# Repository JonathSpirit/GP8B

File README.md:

# GP8B - GProcessor8Bits

Copyright (C) 2022 Guillaume Guillet\
Licensed under CERN-OHL-W v2 or later

<table border="0px">
<tr>
<td>
This source describes Open Hardware and is licensed under the CERN-OHL-W v2 or later.
</td>
</tr>
<tr>
<td>
You may redistribute and modify this documentation and make products
using it under the terms of the CERN-OHL-W v2 (https:/cern.ch/cern-ohl).
This documentation is distributed WITHOUT ANY EXPRESS OR IMPLIED
WARRANTY, INCLUDING OF MERCHANTABILITY, SATISFACTORY QUALITY
AND FITNESS FOR A PARTICULAR PURPOSE. Please see the CERN-OHL-W v2
for applicable conditions.
</td>
</tr>
</table>

Made with [Kicad](https://kicad.org/)

## Description
G_Processor8Bits is a homemade, without any microcontroller, 8bits processor.

## Stats

\
\
\

## Block diagram

[Block diagram (.pdf)](documents/blockDiagram/GP8B_blockDiagram.pdf)

## Instruction sets
GP8B follow [CodeG_binary (revision 1)](https://github.com/JonathSpirit/GComputer_standard)

8bits instuction is separated in 2 category :
```
-------------- Argument selection
|||  
||| ---------- Opcode
||| |||||
000 00000
```
**5bits for opcode :**
```
OPCODE      HEX     NAME            DESCRIPTION
xxx0’0000   0x00    BWRITE1_CLK     Apply value to bus “write 1”.
xxx0’0001   0x01    BWRITE2_CLK     Apply value to bus “write 2”.
xxx0’0010   0x02    BPCS_CLK        Apply value to bus “peripheral CS”.
xxx0’0011   0x03    OPLEFT_CLK      Apply value to the left operation.
xxx0’0100   0x04    OPRIGHT_CLK     Apply value to the right operation.
xxx0’0101   0x05    OPCHOOSE_CLK    Apply value for choosing the operation.
xxx0’0110   0x06    PERIPHERAL_CLK  Send a clock pulse to the peripheral.
xxx0’0111   0x07    BJMPSRC1_CLK    Apply value to bus “jump source 1”.
xxx0’1000   0x08    BJMPSRC2_CLK    Apply value to bus “jump source 2”.
xxx0’1001   0x09    BJMPSRC3_CLK    Apply value to bus “jump source 3”.
xxx0’1010   0x0A    JMPSRC_CLK      Jump to the address of “jump source”.
xxx0’1011   0x0B    BRAMADD1_CLK    Apply value to bus “RAM address 1”.
xxx0’1100   0x0C    BRAMADD2_CLK    Apply value to bus “RAM address 2”.
xxx0’1101   0x0D    SPI_CLK         Send a clock pulse for the SPI.
xxx0’1110   0x0E    BCFG_SPI_CLK    Apply value to the config bus SPI.
xxx0’1111   0x0F    STICK           Simple tick, do nothing (delay).
xxx1’0000   0x10    IF              Conditional instruction.
xxx1’0001   0x11    IFNOT           Conditional instruction inverted.
xxx1’0010   0x12    RAMW            Write value to the actual address of the memory.
xxx1’0011   0x13    UOP             Undefined operation.
xxx1’0100   0x14    UOP             Undefined operation.
xxx1’0101   0x15    UOP             Undefined operation.
xxx1’0110   0x16    UOP             Undefined operation.
xxx1’0111   0x17    LTICK           Long tick, do nothing (delay).
```
**3bits for argument selection :**
```
OPCODE      HEX     NAME            DESCRIPTION
000x’xxxx   0x00    SRCVALUE        The value stored to the source.
001x’xxxx   0x20    BREAD1          The value of the read bus 1.
010x’xxxx   0x40    BREAD2          The value of the read bus 2.
011x’xxxx   0x60    OPRESULT        The value of the operation result (ALU).
100x’xxxx   0x80    RAMVALUE        The value of the processor memory.
101x’xxxx   0xA0    SPI             The value of the SPI.
110x’xxxx   0xC0    EXT_1           External value 1.
111x’xxxx   0xE0    EXT_2           External value 2.
```

## Processor standard
This processor, follow the [SPS1](https://github.com/JonathSpirit/GComputer_standard) standard

## Compatibility
Compatible with all motherboard following the [MOM1_SPS1](https://github.com/JonathSpirit/GComputer_standard) standard

## Documents
[Block diagram (.pdf)](documents/blockDiagram/GP8B_blockDiagram.pdf)

[Schematics (.pdf)](documents/GP8B_schematics.pdf)

[Materials (.pdf)](documents/GP8B_materials.pdf)

[Datasheet (.pdf)](documents/GP8B_datasheet.pdf)

## Contributing / Questions
Please see [Contributing file](CONTRIBUTING.md)

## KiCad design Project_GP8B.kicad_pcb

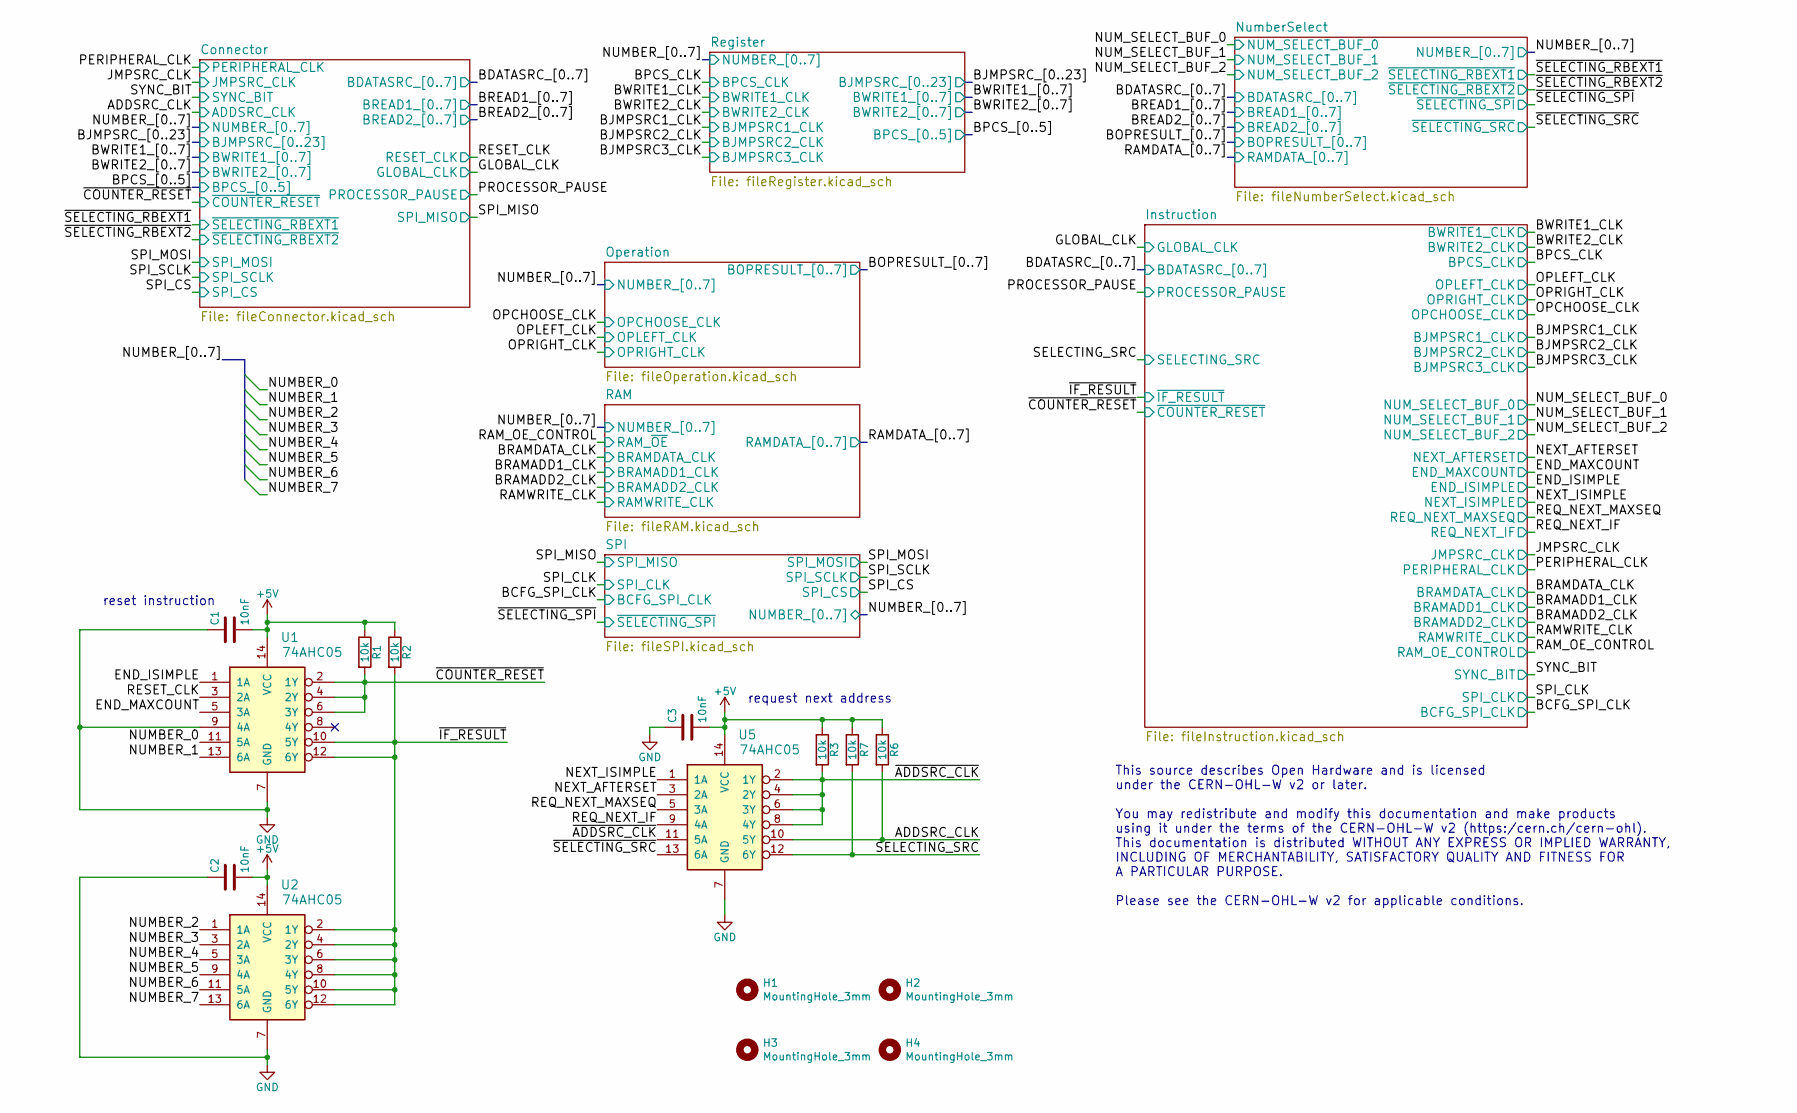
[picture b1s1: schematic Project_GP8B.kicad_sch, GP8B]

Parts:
C1, C2, C3: 10nF; C_0805_2012Metric
H1, H2, H3, H4: MountingHole_3mm
R1, R2, R3, R6, R7: 10k; R_0805_2012Metric
U1, U2, U5: 74AHC05; SOIC-14_3.9x8.7mm_P1.27mm

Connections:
+5V: C1.2, C2.2, C3.2, R1.1, R2.1, R3.1, R6.1, R7.1, U1.14 (VCC), U2.14 (VCC), U5.14 (VCC); also elsewhere on the board
/END_ISIMPLE: U1.1 (1A); also elsewhere on the board
/NEXT_AFTERSET: U5.3 (2A); also elsewhere on the board
/NEXT_IF: U5.9 (4A); also elsewhere on the board
/NEXT_ISIMPLE: U5.1 (1A); also elsewhere on the board
/NUMBER_0: U1.11 (5A); also elsewhere on the board
/NUMBER_1: U1.13 (6A); also elsewhere on the board
/NUMBER_2: U2.1 (1A); also elsewhere on the board
/NUMBER_3: U2.3 (2A); also elsewhere on the board
/NUMBER_4: U2.5 (3A); also elsewhere on the board
/NUMBER_5: U2.9 (4A); also elsewhere on the board
/NUMBER_6: U2.11 (5A); also elsewhere on the board
/NUMBER_7: U2.13 (6A); also elsewhere on the board
/RESET_CLK: U1.3 (2A); also elsewhere on the board
/~COUNTER_RESET: R1.2, U1.2 (1Y), U1.4 (2Y), U1.6 (3Y); also elsewhere on the board
/~SELECTING_SRC: U5.13 (6A); also elsewhere on the board

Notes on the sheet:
reset instruction
request next address
This source describes Open Hardware and is licensed under the CERN-OHL-W v2 or later. You may redistribute and modify this documentation and make products using it under the terms of the CERN-OHL-W v2 (https:/cern.ch/cern-ohl). This documentation is distributed WITHOUT ANY EXPRESS OR IMPLIED WARRAN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

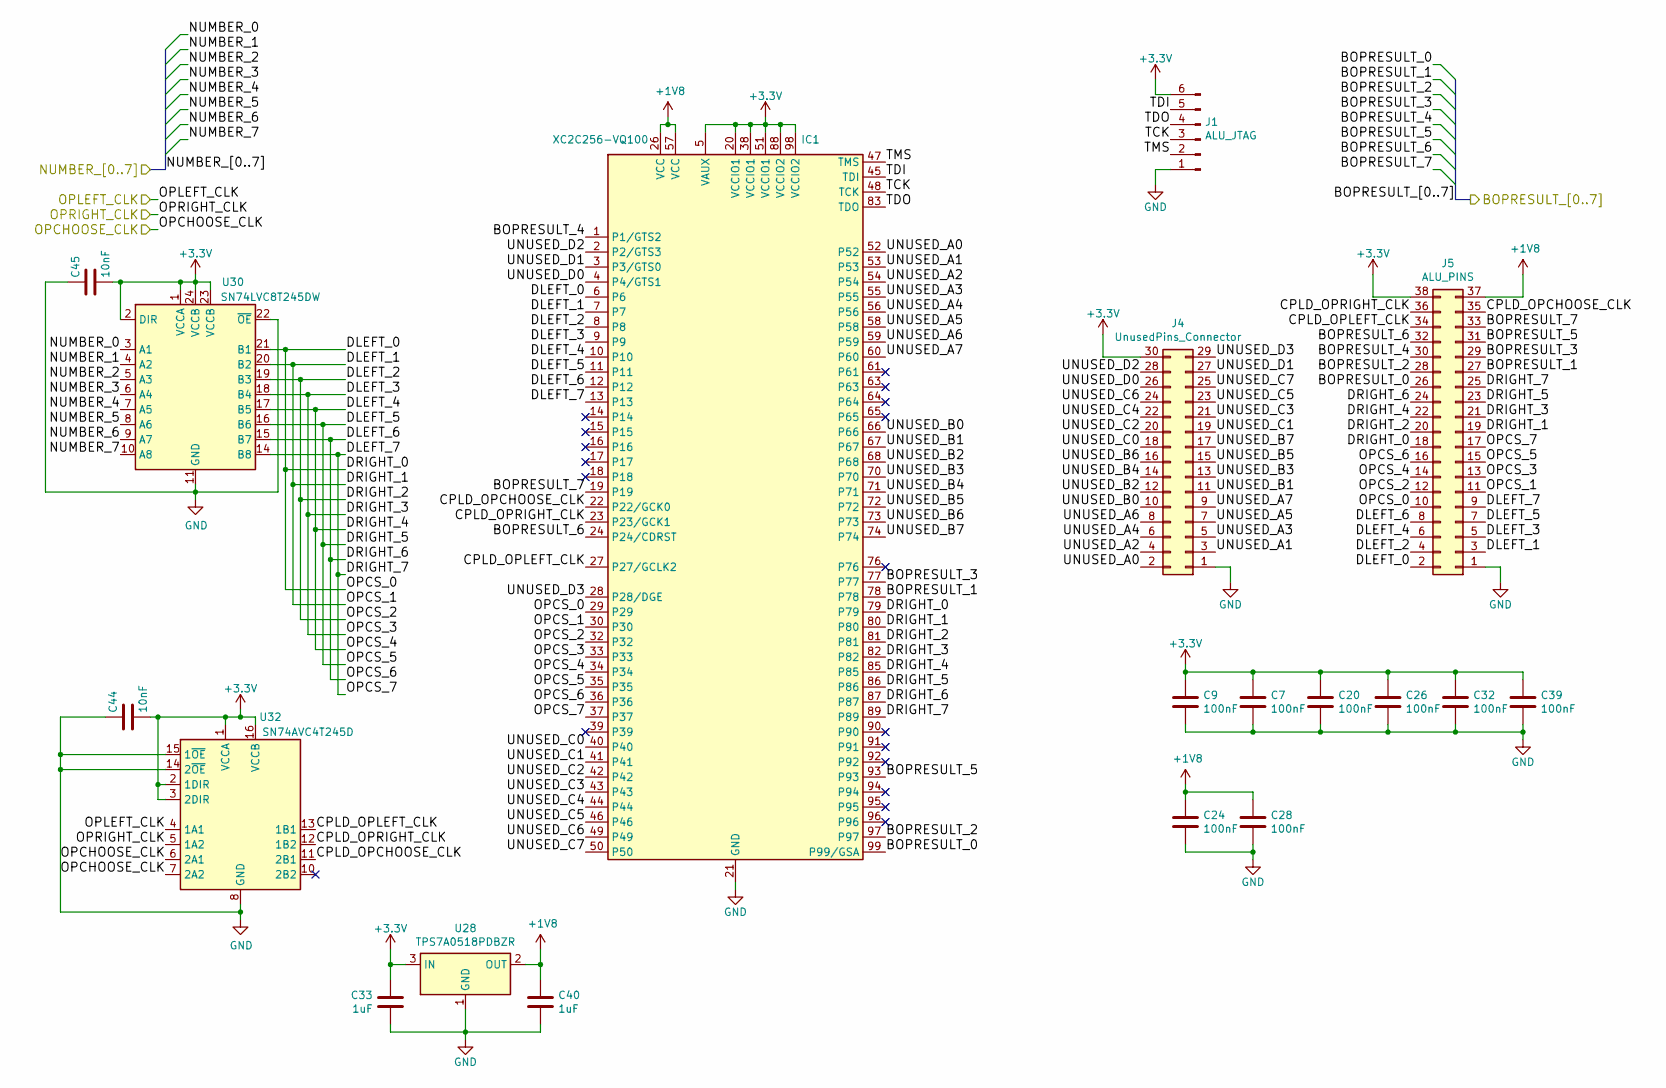
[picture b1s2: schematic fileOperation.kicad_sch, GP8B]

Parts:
C7, C9, C20, C24, C26, C28, C32, C39: 100nF; C_0805_2012Metric
C33, C40: 1uF; C_0805_2012Metric
C44, C45: 10nF; C_0805_2012Metric
IC1: XC2C256-VQ100; VQFP-100_14x14mm_P0.5mm
J1: ALU_JTAG; PinHeader_1x06_P2.54mm_Vertical
J4: UnusedPins_Connector; PinHeader_2x15_P1.27mm_Vertical
J5: ALU_PINS; PinHeader_2x19_P1.27mm_Vertical
U28: TPS7A0518PDBZR; SOT-23
U30: SN74LVC8T245DW; SOIC-24W_7.5x15.4mm_P1.27mm
U32: SN74AVC4T245D; SOIC-16_3.9x9.9mm_P1.27mm

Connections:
+1V8: C24.1, C28.1, C40.1, IC1.26 (VCC), IC1.57 (VCC), J5.37, U28.2 (OUT)
+3V3: C7.1, C9.1, C20.1, C26.1, C32.1, C33.1, C39.1, C44.2, C45.2, IC1.5 (VAUX), IC1.20 (VCCIO1), IC1.38 (VCCIO1), IC1.51 (VCCIO1), IC1.88 (VCCIO2), IC1.98 (VCCIO2), J1.6, J4.30, J5.38, U28.3 (IN), U30.1 (VCCA), U30.2 (DIR), U30.23 (VCCB), U30.24 (VCCB), U32.1 (VCCA), U32.2 (1DIR), U32.3 (2DIR), U32.16 (VCCB); also elsewhere on the board
/NUMBER_0: U30.3 (A1); also elsewhere on the board
/NUMBER_1: U30.4 (A2); also elsewhere on the board
/NUMBER_2: U30.5 (A3); also elsewhere on the board
/NUMBER_3: U30.6 (A4); also elsewhere on the board
/NUMBER_4: U30.7 (A5); also elsewhere on the board
/NUMBER_5: U30.8 (A6); also elsewhere on the board
/NUMBER_6: U30.9 (A7); also elsewhere on the board
/NUMBER_7: U30.10 (A8); also elsewhere on the board
/NumberSelect/BOPRESULT_0: IC1.99 (P99/GSA), J5.26; also elsewhere on the board
/NumberSelect/BOPRESULT_1: IC1.78, J5.27; also elsewhere on the board
/NumberSelect/BOPRESULT_2: IC1.97, J5.28; also elsewhere on the board
/NumberSelect/BOPRESULT_3: IC1.77, J5.29; also elsewhere on the board
/NumberSelect/BOPRESULT_4: IC1.1 (P1/GTS2), J5.30; also elsewhere on the board
/NumberSelect/BOPRESULT_5: IC1.93, J5.31; also elsewhere on the board
/NumberSelect/BOPRESULT_6: IC1.24 (P24/CDRST), J5.32; also elsewhere on the board
/NumberSelect/BOPRESULT_7: IC1.19, J5.33; also elsewhere on the board
/OPCHOOSE_CLK: U32.6 (2A1), U32.7 (2A2); also elsewhere on the board
/OPLEFT_CLK: U32.4 (1A1); also elsewhere on the board
/OPRIGHT_CLK: U32.5 (1A2); also elsewhere on the board
/Operation/CPLD_OPCHOOSE_CLK: IC1.22 (P22/GCK0), J5.35, U32.11 (2B1)
/Operation/CPLD_OPLEFT_CLK: IC1.27 (P27/GCLK2), J5.34, U32.13 (1B1)
/Operation/CPLD_OPRIGHT_CLK: IC1.23 (P23/GCK1), J5.36, U32.12 (1B2)
/Operation/DLEFT_0: IC1.6, IC1.29, IC1.79, J5.2, J5.10, J5.18, U30.21 (B1)
/Operation/DLEFT_1: IC1.7, IC1.30, IC1.80, J5.3, J5.11, J5.19, U30.20 (B2)
/Operation/DLEFT_2: IC1.8, IC1.32, IC1.81, J5.4, J5.12, J5.20, U30.19 (B3)
/Operation/DLEFT_3: IC1.9, IC1.33, IC1.82, J5.5, J5.13, J5.21, U30.18 (B4)
/Operation/DLEFT_4: IC1.10, IC1.34, IC1.85, J5.6, J5.14, J5.22, U30.17 (B5)
/Operation/DLEFT_5: IC1.11, IC1.35, IC1.86, J5.7, J5.15, J5.23, U30.16 (B6)
/Operation/DLEFT_6: IC1.12, IC1.36, IC1.87, J5.8, J5.16, J5.24, U30.15 (B7)
/Operation/DLEFT_7: IC1.13, IC1.37, IC1.89, J5.9, J5.17, J5.25, U30.14 (B8)
/Operation/TCK: IC1.48 (TCK), J1.3
/Operation/TDI: IC1.45 (TDI), J1.5
/Operation/TDO: IC1.83 (TDO), J1.4
/Operation/TMS: IC1.47 (TMS), J1.2
/Operation/UNUSED_A0: IC1.52, J4.2
/Operation/UNUSED_A1: IC1.53, J4.3
/Operation/UNUSED_A2: IC1.54, J4.4
/Operation/UNUSED_A3: IC1.55, J4.5
/Operation/UNUSED_A4: IC1.56, J4.6
/Operation/UNUSED_A5: IC1.58, J4.7
/Operation/UNUSED_A6: IC1.59, J4.8
/Operation/UNUSED_A7: IC1.60, J4.9
/Operation/UNUSED_B0: IC1.66, J4.10
/Operation/UNUSED_B1: IC1.67, J4.11
/Operation/UNUSED_B2: IC1.68, J4.12
/Operation/UNUSED_B3: IC1.70, J4.13
/Operation/UNUSED_B4: IC1.71, J4.14
/Operation/UNUSED_B5: IC1.72, J4.15
/Operation/UNUSED_B6: IC1.73, J4.16
/Operation/UNUSED_B7: IC1.74, J4.17
/Operation/UNUSED_C0: IC1.40, J4.18
/Operation/UNUSED_C1: IC1.41, J4.19
/Operation/UNUSED_C2: IC1.42, J4.20
/Operation/UNUSED_C3: IC1.43, J4.21
/Operation/UNUSED_C4: IC1.44, J4.22
/Operation/UNUSED_C5: IC1.46, J4.23
/Operation/UNUSED_C6: IC1.49, J4.24
/Operation/UNUSED_C7: IC1.50, J4.25
/Operation/UNUSED_D0: IC1.4 (P4/GTS1), J4.26
/Operation/UNUSED_D1: IC1.3 (P3/GTS0), J4.27
/Operation/UNUSED_D2: IC1.2 (P2/GTS3), J4.28
/Operation/UNUSED_D3: IC1.28 (P28/DGE), J4.29

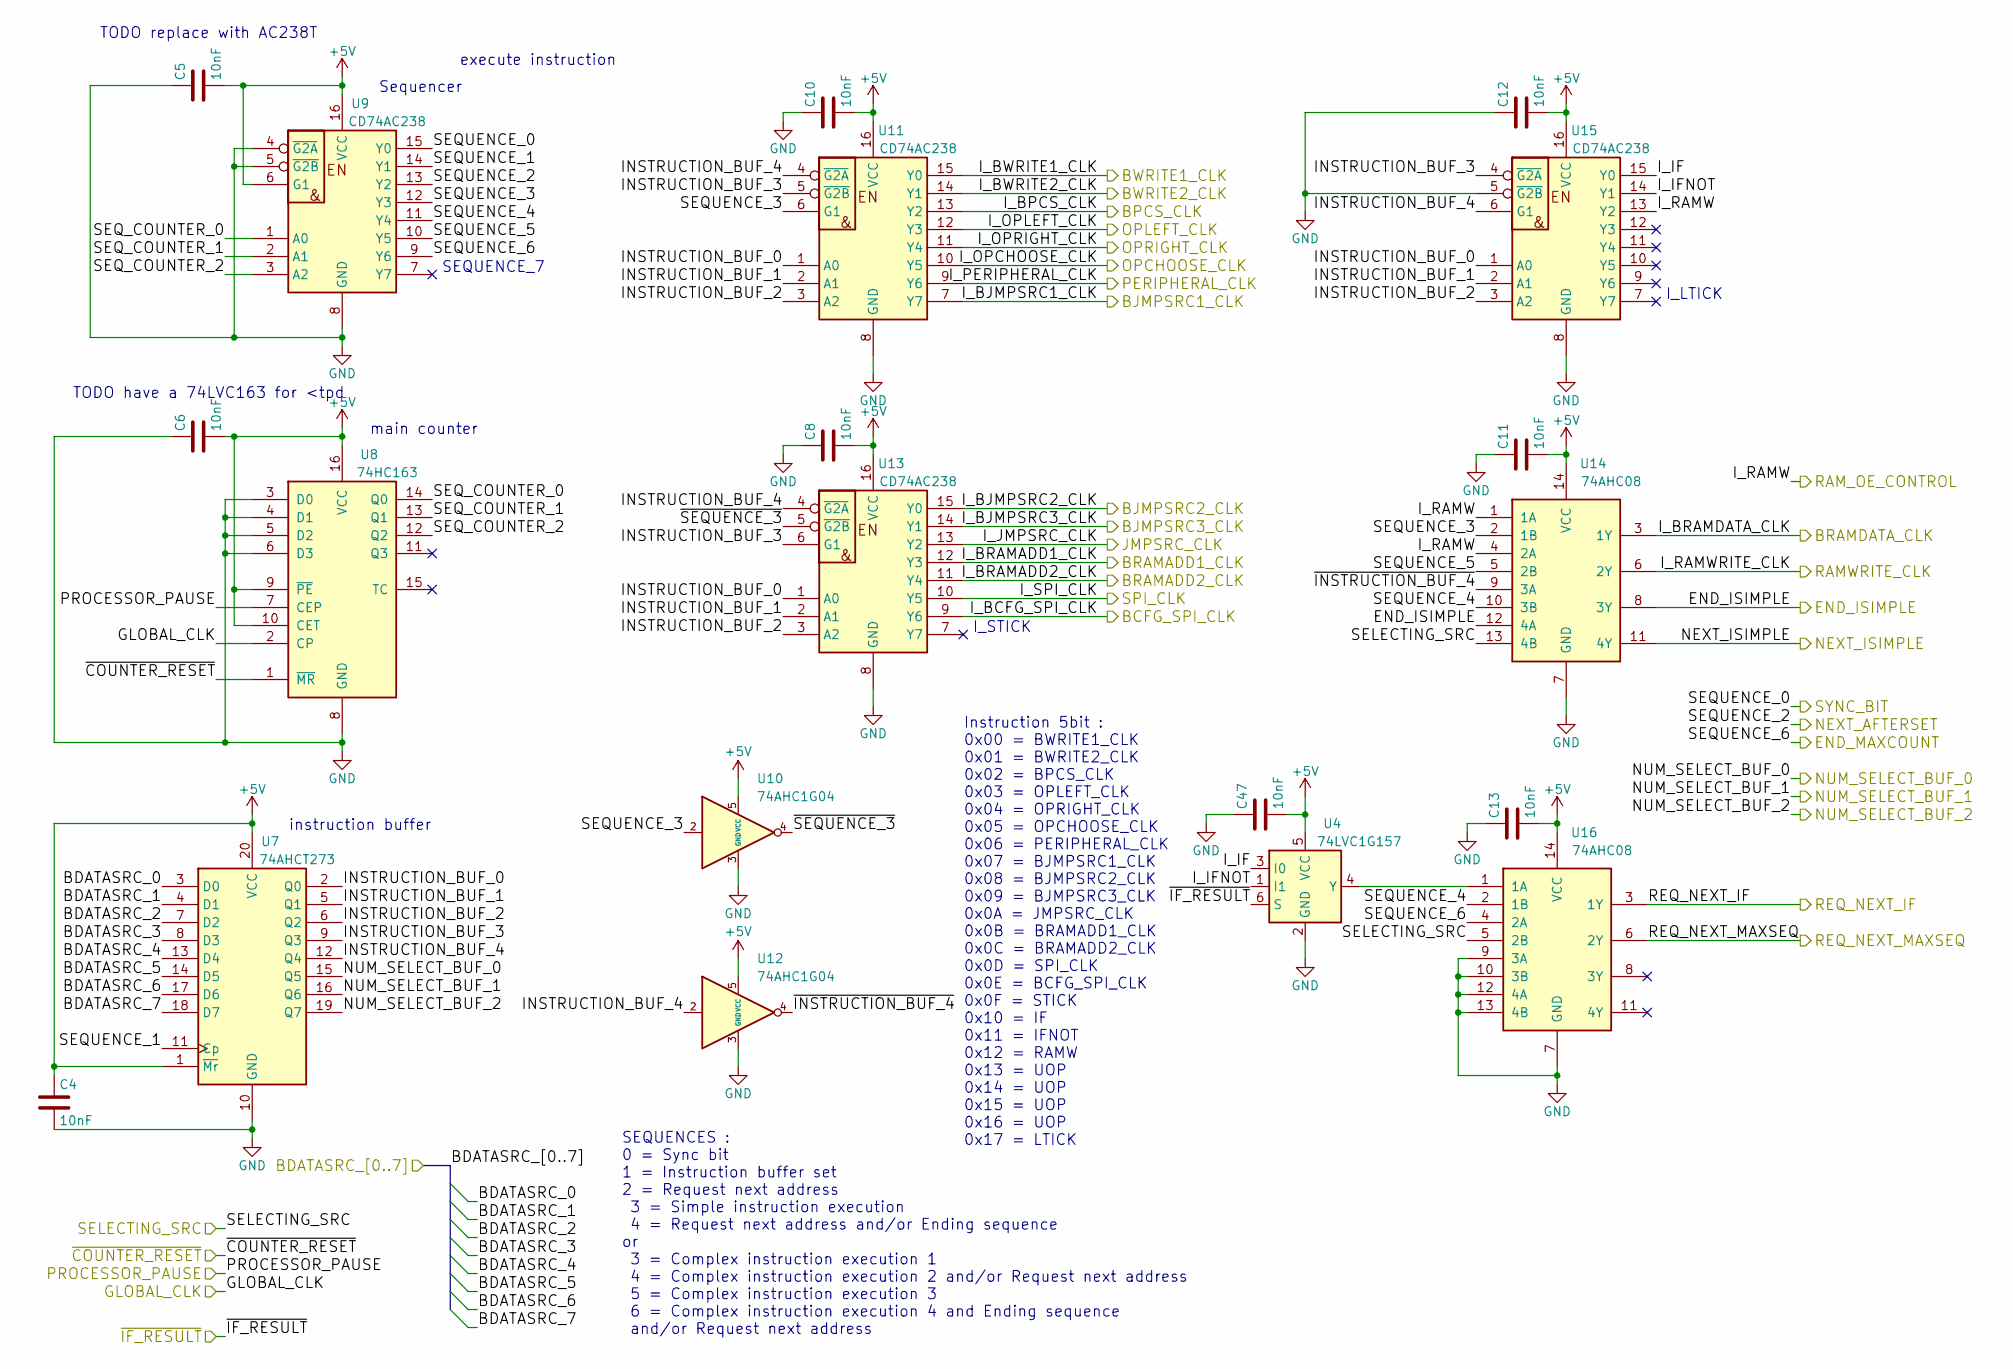
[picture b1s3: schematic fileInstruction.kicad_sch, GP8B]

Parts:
C4, C5, C6, C8, C10, C11, C12, C13, C47: 10nF; C_0805_2012Metric
U4: 74LVC1G157; SC-74-6_1.5x2.9mm_P0.95mm
U7: 74AHCT273; SOIC-20W_7.5x12.8mm_P1.27mm
U8: 74HC163; SOIC-16_3.9x9.9mm_P1.27mm
U9, U11, U13, U15: CD74AC238; SOIC-16_3.9x9.9mm_P1.27mm
U10, U12: 74AHC1G04; SOT-23-5
U14, U16: 74AHC08; SOIC-14_3.9x8.7mm_P1.27mm

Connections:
+5V: C4.1, C5.2, C6.2, C8.2, C10.2, C11.2, C12.2, C13.2, C47.2, U4.5 (VCC), U7.1 (~Mr), U7.20 (VCC), U8.9 (~PE), U8.10 (CET), U8.16 (VCC), U9.6 (G1), U9.16 (VCC), U10.5 (VCC), U11.16 (VCC), U12.5 (VCC), U13.16 (VCC), U14.14 (VCC), U15.16 (VCC), U16.14 (VCC); also elsewhere on the board
/BCFG_SPI_CLK: U13.9 (Y6); also elsewhere on the board
/BJMPSRC1_CLK: U11.7 (Y7); also elsewhere on the board
/BJMPSRC2_CLK: U13.15 (Y0); also elsewhere on the board
/BJMPSRC3_CLK: U13.14 (Y1); also elsewhere on the board
/BPCS_CLK: U11.13 (Y2); also elsewhere on the board
/BRAMADD1_CLK: U13.12 (Y3); also elsewhere on the board
/BRAMADD2_CLK: U13.11 (Y4); also elsewhere on the board
/BRAMDATA_CLK: U14.3 (1Y); also elsewhere on the board
/BWRITE1_CLK: U11.15 (Y0); also elsewhere on the board
/BWRITE2_CLK: U11.14 (Y1); also elsewhere on the board
/Connector/BDATASRC_0: U7.3 (D0); also elsewhere on the board
/Connector/BDATASRC_1: U7.4 (D1); also elsewhere on the board
/Connector/BDATASRC_2: U7.7 (D2); also elsewhere on the board
/Connector/BDATASRC_3: U7.8 (D3); also elsewhere on the board
/Connector/BDATASRC_4: U7.13 (D4); also elsewhere on the board
/Connector/BDATASRC_5: U7.14 (D5); also elsewhere on the board
/Connector/BDATASRC_6: U7.17 (D6); also elsewhere on the board
/Connector/BDATASRC_7: U7.18 (D7); also elsewhere on the board
/END_ISIMPLE: U14.8 (3Y), U14.12 (4A); also elsewhere on the board
/GLOBAL_CLK: U8.2 (CP); also elsewhere on the board
/Instruction/COUNTER_OUT_0: U8.14 (Q0), U9.1 (A0)
/Instruction/COUNTER_OUT_1: U8.13 (Q1), U9.2 (A1)
/Instruction/INSTRUCTION_B1: U7.2 (Q0), U11.1 (A0), U13.1 (A0), U15.1 (A0)
/Instruction/INSTRUCTION_B2: U7.5 (Q1), U11.2 (A1), U13.2 (A1), U15.2 (A1)
/Instruction/INSTRUCTION_B3: U7.6 (Q2), U11.3 (A2), U13.3 (A2), U15.3 (A2)
/Instruction/INSTRUCTION_B4: U7.9 (Q3), U11.5 (~G2B), U13.6 (G1), U15.4 (~G2A)
/Instruction/INSTRUCTION_B5: U7.12 (Q4), U11.4 (~G2A), U12.2, U13.4 (~G2A), U15.6 (G1)
/Instruction/~COUNTER_2: U10.4, U13.5 (~G2B)
/Instruction/~INSTRUCTION_B5: U12.4, U14.9 (3A)
/JMPSRC_CLK: U13.13 (Y2); also elsewhere on the board
/NEXT_AFTERSET: U7.11 (Cp), U9.14 (Y1); also elsewhere on the board
/NEXT_IF: U16.3 (1Y); also elsewhere on the board
/NEXT_ISIMPLE: U14.11 (4Y); also elsewhere on the board
/NUM_SELECT_0: U7.15 (Q5); also elsewhere on the board
/NUM_SELECT_1: U7.16 (Q6); also elsewhere on the board
/NUM_SELECT_2: U7.19 (Q7); also elsewhere on the board
/OPCHOOSE_CLK: U11.10 (Y5); also elsewhere on the board
/OPLEFT_CLK: U11.12 (Y3); also elsewhere on the board
/OPRIGHT_CLK: U11.11 (Y4); also elsewhere on the board
/PERIPHERAL_CLK: U11.9 (Y6); also elsewhere on the board
/PROCESSOR_PAUSE: U8.7 (CEP); also elsewhere on the board
/RAMWRITE_CLK: U14.6 (2Y); also elsewhere on the board
/RAM_OE_CONTROL: U14.1 (1A), U14.4 (2A), U15.13 (Y2); also elsewhere on the board
/SPI_CLK: U13.10 (Y5); also elsewhere on the board
/SYNC_BIT: U9.15 (Y0); also elsewhere on the board
/~COUNTER_RESET: U8.1 (~MR); also elsewhere on the board

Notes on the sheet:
SEQUENCE_7
instruction buffer
SEQUENCES : 0 = Sync bit 1 = Instruction buffer set 2 = Request next address 3 = Simple instruction execution 4 = Request next address and/or Ending sequence or 3 = Complex instruction execution 1 4 = Complex instruction execution 2 and/or Request next address 5 = Complex instruction execution 3 6 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
TODO replace with AC238T
Sequencer
TODO have a 74LVC163 for <tpd
main counter
execute instruction
I_LTICK
I_STICK
Instruction 5bit : 0x00 = BWRITE1_CLK 0x01 = BWRITE2_CLK 0x02 = BPCS_CLK 0x03 = OPLEFT_CLK 0x04 = OPRIGHT_CLK 0x05 = OPCHOOSE_CLK 0x06 = PERIPHERAL_CLK 0x07 = BJMPSRC1_CLK 0x08 = BJMPSRC2_CLK 0x09 = BJMPSRC3_CLK 0x0A = JMPSRC_CLK 0x0B = BRAMADD1_CLK 0x0C = BRAMADD2_CLK 0x0D = SPI_CLK 0x0E = BCFG_SP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

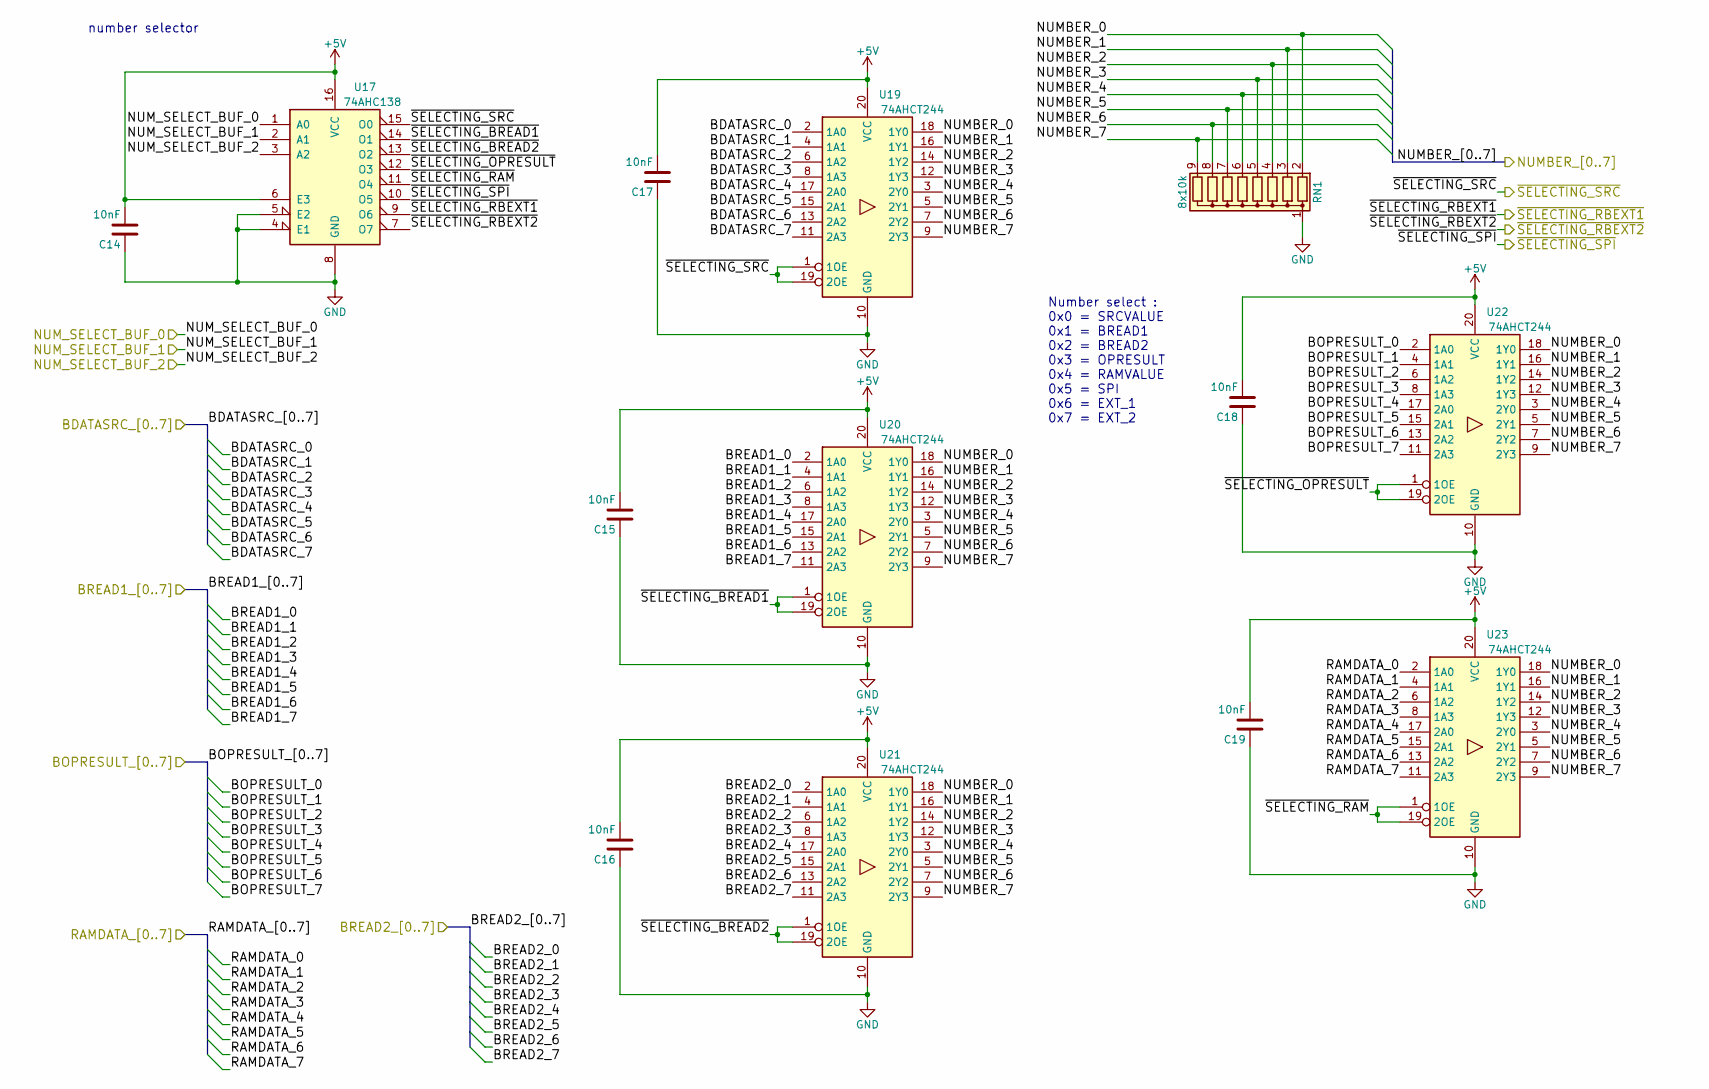
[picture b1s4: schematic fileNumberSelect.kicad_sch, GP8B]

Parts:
C14, C15, C16, C17, C18, C19: 10nF; C_0805_2012Metric
RN1: 8x10k; R_Array_SIP9
U17: 74AHC138; SOIC-16W_5.3x10.2mm_P1.27mm
U19, U20, U21, U22, U23: 74AHCT244; SOIC-20W_7.5x12.8mm_P1.27mm

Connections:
+5V: C14.2, C15.2, C16.2, C17.2, C18.2, C19.2, U17.6 (E3), U17.16 (VCC), U19.20 (VCC), U20.20 (VCC), U21.20 (VCC), U22.20 (VCC), U23.20 (VCC); also elsewhere on the board
/Connector/BDATASRC_0: U19.2 (1A0); also elsewhere on the board
/Connector/BDATASRC_1: U19.4 (1A1); also elsewhere on the board
/Connector/BDATASRC_2: U19.6 (1A2); also elsewhere on the board
/Connector/BDATASRC_3: U19.8 (1A3); also elsewhere on the board
/Connector/BDATASRC_4: U19.17 (2A0); also elsewhere on the board
/Connector/BDATASRC_5: U19.15 (2A1); also elsewhere on the board
/Connector/BDATASRC_6: U19.13 (2A2); also elsewhere on the board
/Connector/BDATASRC_7: U19.11 (2A3); also elsewhere on the board
/Connector/BREAD1_0: U20.2 (1A0); also elsewhere on the board
/Connector/BREAD1_1: U20.4 (1A1); also elsewhere on the board
/Connector/BREAD1_2: U20.6 (1A2); also elsewhere on the board
/Connector/BREAD1_3: U20.8 (1A3); also elsewhere on the board
/Connector/BREAD1_4: U20.17 (2A0); also elsewhere on the board
/Connector/BREAD1_5: U20.15 (2A1); also elsewhere on the board
/Connector/BREAD1_6: U20.13 (2A2); also elsewhere on the board
/Connector/BREAD1_7: U20.11 (2A3); also elsewhere on the board
/Connector/BREAD2_0: U21.2 (1A0); also elsewhere on the board
/Connector/BREAD2_1: U21.4 (1A1); also elsewhere on the board
/Connector/BREAD2_2: U21.6 (1A2); also elsewhere on the board
/Connector/BREAD2_3: U21.8 (1A3); also elsewhere on the board
/Connector/BREAD2_4: U21.17 (2A0); also elsewhere on the board
/Connector/BREAD2_5: U21.15 (2A1); also elsewhere on the board
/Connector/BREAD2_6: U21.13 (2A2); also elsewhere on the board
/Connector/BREAD2_7: U21.11 (2A3); also elsewhere on the board
/NUMBER_0: RN1.2 (R1), U19.18 (1Y0), U20.18 (1Y0), U21.18 (1Y0), U22.18 (1Y0), U23.18 (1Y0); also elsewhere on the board
/NUMBER_1: RN1.3 (R2), U19.16 (1Y1), U20.16 (1Y1), U21.16 (1Y1), U22.16 (1Y1), U23.16 (1Y1); also elsewhere on the board
/NUMBER_2: RN1.4 (R3), U19.14 (1Y2), U20.14 (1Y2), U21.14 (1Y2), U22.14 (1Y2), U23.14 (1Y2); also elsewhere on the board
/NUMBER_3: RN1.5 (R4), U19.12 (1Y3), U20.12 (1Y3), U21.12 (1Y3), U22.12 (1Y3), U23.12 (1Y3); also elsewhere on the board
/NUMBER_4: RN1.6 (R5), U19.3 (2Y0), U20.3 (2Y0), U21.3 (2Y0), U22.3 (2Y0), U23.3 (2Y0); also elsewhere on the board
/NUMBER_5: RN1.7 (R6), U19.5 (2Y1), U20.5 (2Y1), U21.5 (2Y1), U22.5 (2Y1), U23.5 (2Y1); also elsewhere on the board
/NUMBER_6: RN1.8 (R7), U19.7 (2Y2), U20.7 (2Y2), U21.7 (2Y2), U22.7 (2Y2), U23.7 (2Y2); also elsewhere on the board
/NUMBER_7: RN1.9 (R8), U19.9 (2Y3), U20.9 (2Y3), U21.9 (2Y3), U22.9 (2Y3), U23.9 (2Y3); also elsewhere on the board
/NUM_SELECT_0: U17.1 (A0); also elsewhere on the board
/NUM_SELECT_1: U17.2 (A1); also elsewhere on the board
/NUM_SELECT_2: U17.3 (A2); also elsewhere on the board
/NumberSelect/BOPRESULT_0: U22.2 (1A0); also elsewhere on the board
/NumberSelect/BOPRESULT_1: U22.4 (1A1); also elsewhere on the board
/NumberSelect/BOPRESULT_2: U22.6 (1A2); also elsewhere on the board
/NumberSelect/BOPRESULT_3: U22.8 (1A3); also elsewhere on the board
/NumberSelect/BOPRESULT_4: U22.17 (2A0); also elsewhere on the board
/NumberSelect/BOPRESULT_5: U22.15 (2A1); also elsewhere on the board
/NumberSelect/BOPRESULT_6: U22.13 (2A2); also elsewhere on the board
/NumberSelect/BOPRESULT_7: U22.11 (2A3); also elsewhere on the board
/NumberSelect/RAMDATA_0: U23.2 (1A0); also elsewhere on the board
/NumberSelect/RAMDATA_1: U23.4 (1A1); also elsewhere on the board
/NumberSelect/RAMDATA_2: U23.6 (1A2); also elsewhere on the board
/NumberSelect/RAMDATA_3: U23.8 (1A3); also elsewhere on the board
/NumberSelect/RAMDATA_4: U23.17 (2A0); also elsewhere on the board
/NumberSelect/RAMDATA_5: U23.15 (2A1); also elsewhere on the board
/NumberSelect/RAMDATA_6: U23.13 (2A2); also elsewhere on the board
/NumberSelect/RAMDATA_7: U23.11 (2A3); also elsewhere on the board
/NumberSelect/~SELECTING_BREAD1: U17.14 (O1), U20.1 (1OE), U20.19 (2OE)
/NumberSelect/~SELECTING_BREAD2: U17.13 (O2), U21.1 (1OE), U21.19 (2OE)
/NumberSelect/~SELECTING_OPRESULT: U17.12 (O3), U22.1 (1OE), U22.19 (2OE)
/NumberSelect/~SELECTING_RAM: U17.11 (O4), U23.1 (1OE), U23.19 (2OE)
/~SELECTING_RBEXT1: U17.9 (O6); also elsewhere on the board
/~SELECTING_RBEXT2: U17.7 (O7); also elsewhere on the board
/~SELECTING_SPI: U17.10 (O5); also elsewhere on the board
/~SELECTING_SRC: U17.15 (O0), U19.1 (1OE), U19.19 (2OE); also elsewhere on the board

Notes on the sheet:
Number select : 0x0 = SRCVALUE 0x1 = BREAD1 0x2 = BREAD2 0x3 = OPRESULT 0x4 = RAMVALUE 0x5 = SPI 0x6 = EXT_1 0x7 = EXT_2
number selector

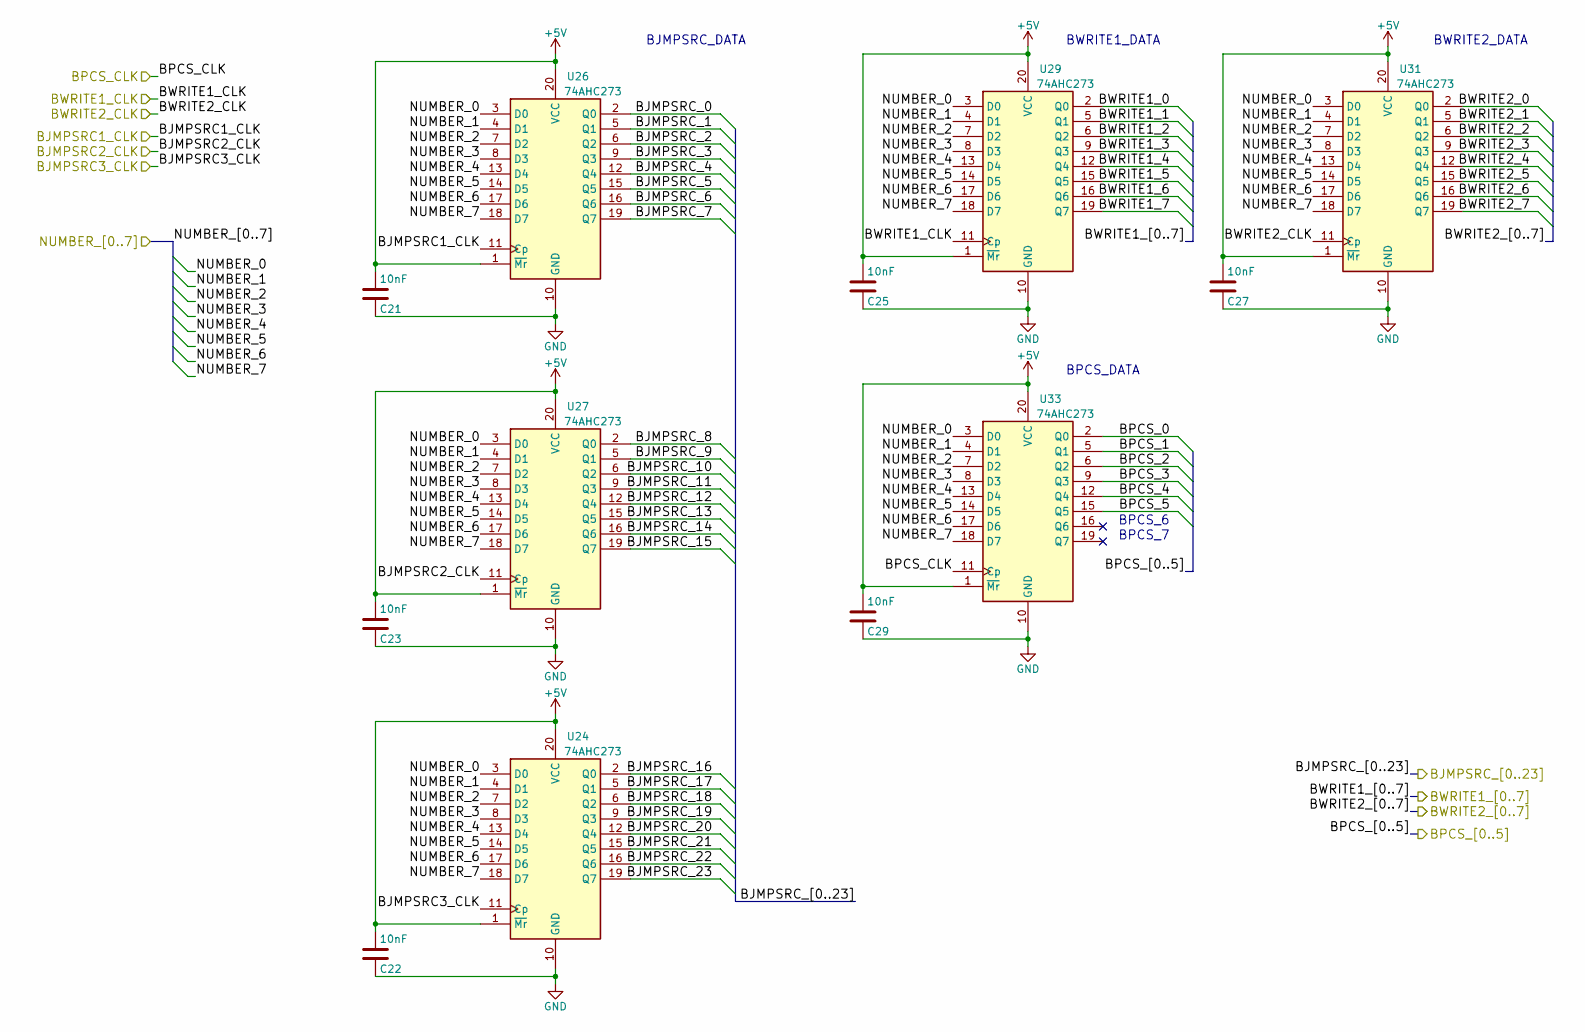
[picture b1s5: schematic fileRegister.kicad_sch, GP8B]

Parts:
C21, C22, C23, C25, C27, C29: 10nF; C_0805_2012Metric
U24, U26, U27, U29, U31, U33: 74AHC273; SOIC-20W_7.5x12.8mm_P1.27mm

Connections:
+5V: C21.2, C22.2, C23.2, C25.2, C27.2, C29.2, U24.1 (~Mr), U24.20 (VCC), U26.1 (~Mr), U26.20 (VCC), U27.1 (~Mr), U27.20 (VCC), U29.1 (~Mr), U29.20 (VCC), U31.1 (~Mr), U31.20 (VCC), U33.1 (~Mr), U33.20 (VCC); also elsewhere on the board
/BJMPSRC1_CLK: U26.11 (Cp); also elsewhere on the board
/BJMPSRC2_CLK: U27.11 (Cp); also elsewhere on the board
/BJMPSRC3_CLK: U24.11 (Cp); also elsewhere on the board
/BPCS_CLK: U33.11 (Cp); also elsewhere on the board
/BWRITE1_CLK: U29.11 (Cp); also elsewhere on the board
/BWRITE2_CLK: U31.11 (Cp); also elsewhere on the board
/Connector/BJMPSRC_0: U26.2 (Q0); also elsewhere on the board
/Connector/BJMPSRC_1: U26.5 (Q1); also elsewhere on the board
/Connector/BJMPSRC_2: U26.6 (Q2); also elsewhere on the board
/Connector/BJMPSRC_3: U26.9 (Q3); also elsewhere on the board
/Connector/BJMPSRC_4: U26.12 (Q4); also elsewhere on the board
/Connector/BJMPSRC_5: U26.15 (Q5); also elsewhere on the board
/Connector/BJMPSRC_6: U26.16 (Q6); also elsewhere on the board
/Connector/BJMPSRC_7: U26.19 (Q7); also elsewhere on the board
/Connector/BJMPSRC_8: U27.2 (Q0); also elsewhere on the board
/Connector/BJMPSRC_9: U27.5 (Q1); also elsewhere on the board
/Connector/BJMPSRC_10: U27.6 (Q2); also elsewhere on the board
/Connector/BJMPSRC_11: U27.9 (Q3); also elsewhere on the board
/Connector/BJMPSRC_12: U27.12 (Q4); also elsewhere on the board
/Connector/BJMPSRC_13: U27.15 (Q5); also elsewhere on the board
/Connector/BJMPSRC_14: U27.16 (Q6); also elsewhere on the board
/Connector/BJMPSRC_15: U27.19 (Q7); also elsewhere on the board
/Connector/BJMPSRC_16: U24.2 (Q0); also elsewhere on the board
/Connector/BJMPSRC_17: U24.5 (Q1); also elsewhere on the board
/Connector/BJMPSRC_18: U24.6 (Q2); also elsewhere on the board
/Connector/BJMPSRC_19: U24.9 (Q3); also elsewhere on the board
/Connector/BJMPSRC_20: U24.12 (Q4); also elsewhere on the board
/Connector/BJMPSRC_21: U24.15 (Q5); also elsewhere on the board
/Connector/BJMPSRC_22: U24.16 (Q6); also elsewhere on the board
/Connector/BJMPSRC_23: U24.19 (Q7); also elsewhere on the board
/Connector/BPCS_0: U33.2 (Q0); also elsewhere on the board
/Connector/BPCS_1: U33.5 (Q1); also elsewhere on the board
/Connector/BPCS_2: U33.6 (Q2); also elsewhere on the board
/Connector/BPCS_3: U33.9 (Q3); also elsewhere on the board
/Connector/BPCS_4: U33.12 (Q4); also elsewhere on the board
/Connector/BPCS_5: U33.15 (Q5); also elsewhere on the board
/Connector/BWRITE1_0: U29.2 (Q0); also elsewhere on the board
/Connector/BWRITE1_1: U29.5 (Q1); also elsewhere on the board
/Connector/BWRITE1_2: U29.6 (Q2); also elsewhere on the board
/Connector/BWRITE1_3: U29.9 (Q3); also elsewhere on the board
/Connector/BWRITE1_4: U29.12 (Q4); also elsewhere on the board
/Connector/BWRITE1_5: U29.15 (Q5); also elsewhere on the board
/Connector/BWRITE1_6: U29.16 (Q6); also elsewhere on the board
/Connector/BWRITE1_7: U29.19 (Q7); also elsewhere on the board
/Connector/BWRITE2_0: U31.2 (Q0); also elsewhere on the board
/Connector/BWRITE2_1: U31.5 (Q1); also elsewhere on the board
/Connector/BWRITE2_2: U31.6 (Q2); also elsewhere on the board
/Connector/BWRITE2_3: U31.9 (Q3); also elsewhere on the board
/Connector/BWRITE2_4: U31.12 (Q4); also elsewhere on the board
/Connector/BWRITE2_5: U31.15 (Q5); also elsewhere on the board
/Connector/BWRITE2_6: U31.16 (Q6); also elsewhere on the board
/Connector/BWRITE2_7: U31.19 (Q7); also elsewhere on the board
/NUMBER_0: U24.3 (D0), U26.3 (D0), U27.3 (D0), U29.3 (D0), U31.3 (D0), U33.3 (D0); also elsewhere on the board
/NUMBER_1: U24.4 (D1), U26.4 (D1), U27.4 (D1), U29.4 (D1), U31.4 (D1), U33.4 (D1); also elsewhere on the board
/NUMBER_2: U24.7 (D2), U26.7 (D2), U27.7 (D2), U29.7 (D2), U31.7 (D2), U33.7 (D2); also elsewhere on the board
/NUMBER_3: U24.8 (D3), U26.8 (D3), U27.8 (D3), U29.8 (D3), U31.8 (D3), U33.8 (D3); also elsewhere on the board
/NUMBER_4: U24.13 (D4), U26.13 (D4), U27.13 (D4), U29.13 (D4), U31.13 (D4), U33.13 (D4); also elsewhere on the board
/NUMBER_5: U24.14 (D5), U26.14 (D5), U27.14 (D5), U29.14 (D5), U31.14 (D5), U33.14 (D5); also elsewhere on the board
/NUMBER_6: U24.17 (D6), U26.17 (D6), U27.17 (D6), U29.17 (D6), U31.17 (D6), U33.17 (D6); also elsewhere on the board
/NUMBER_7: U24.18 (D7), U26.18 (D7), U27.18 (D7), U29.18 (D7), U31.18 (D7), U33.18 (D7); also elsewhere on the board

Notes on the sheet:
BPCS_DATA
BWRITE2_DATA
BWRITE1_DATA
BJMPSRC_DATA
BPCS_6
BPCS_7

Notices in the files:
Project_GP8B.kicad_pcb:
Copyright Guillaume Guillet 2022
